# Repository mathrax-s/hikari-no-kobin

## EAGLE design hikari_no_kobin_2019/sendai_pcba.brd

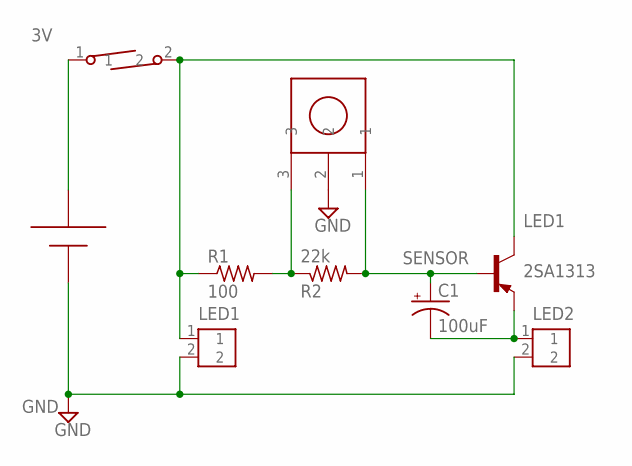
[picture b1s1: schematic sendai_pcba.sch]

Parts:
C1: 100uF; TT2D6
R1: 100; R0603
R2: 22k; R0603
T1: 2SA1313; SOT23-BEC
U$1: CR2032_VCR2032_V; CR2032_V
U$2, U$3: CONNECTER_CON2
U$4: LEAD_SWITCH_LEAD_SWITCH
U$5: OSRB38C9AA

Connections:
3V: U$1.3 (+), U$4.1
GND: U$1.2 (-), U$2.2, U$3.2, U$5.2
LED1: R1.1, T1.C, U$2.1, U$4.2
LED2: C1.-, T1.E, U$3.1
SENSOR: C1.+, R2.2, T1.B, U$5.1
V: R1.2, R2.1, U$5.3

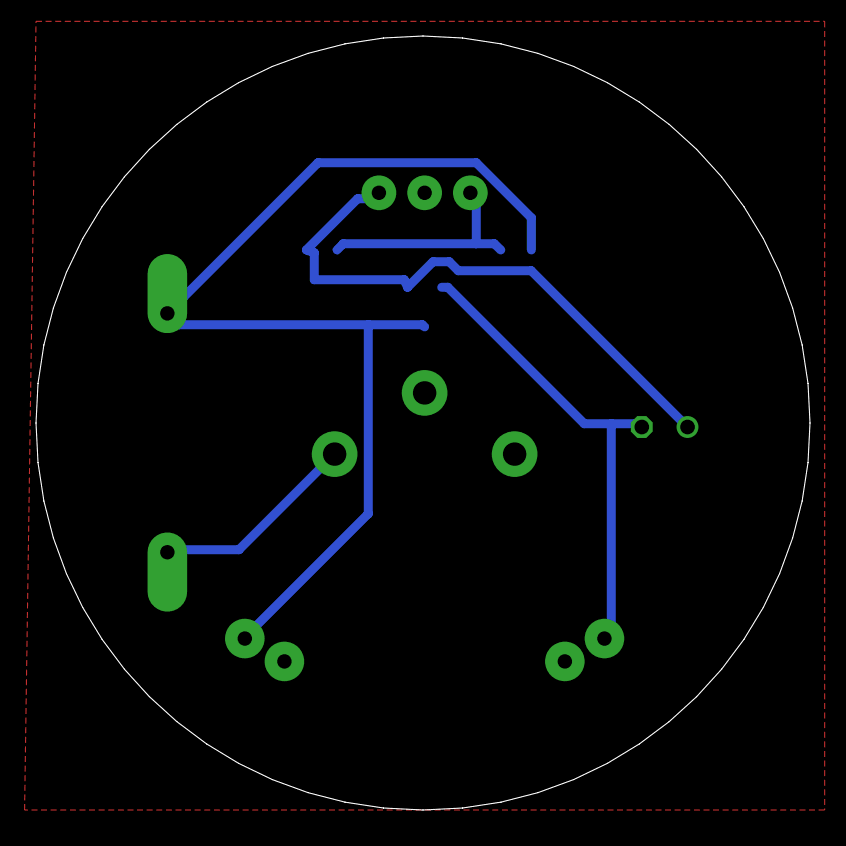
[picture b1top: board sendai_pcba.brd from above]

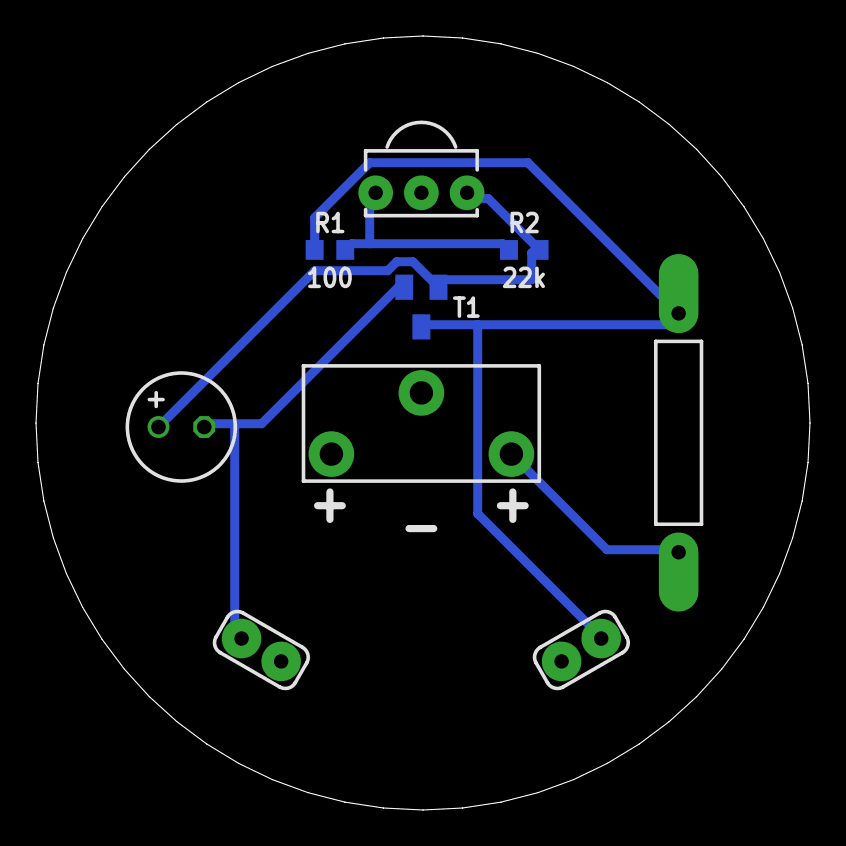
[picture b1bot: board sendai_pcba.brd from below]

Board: 2 copper layers, 43.0 x 43.0 mm, 9 parts (9 on the bottom side), 6 nets.

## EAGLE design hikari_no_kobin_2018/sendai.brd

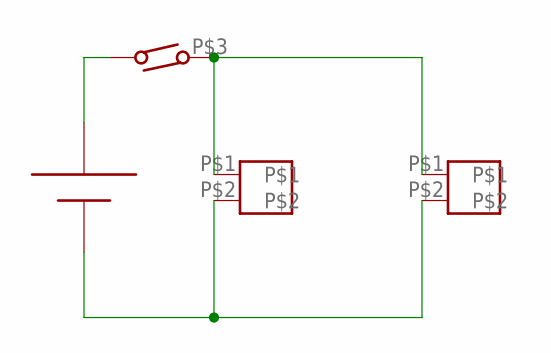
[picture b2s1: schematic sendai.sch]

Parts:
U$1: CR2032_CR2032
U$2, U$3: CONNECTER_CON2
U$4: LEAD_SWITCH_LEAD_SWITCH

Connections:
unnamed: U$2.P$1, U$3.P$1, U$4.P$3
unnamed: U$1.-1 (-), U$2.P$2, U$3.P$2
unnamed: U$1.P$1 (+), U$1.P$2 (+), U$4.P$4

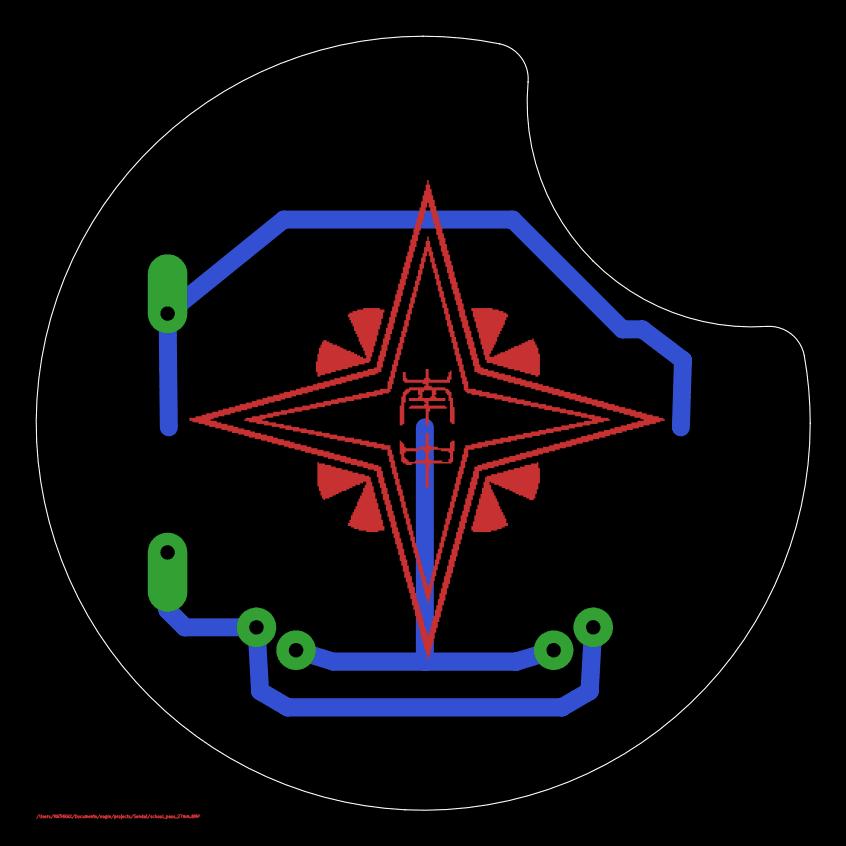
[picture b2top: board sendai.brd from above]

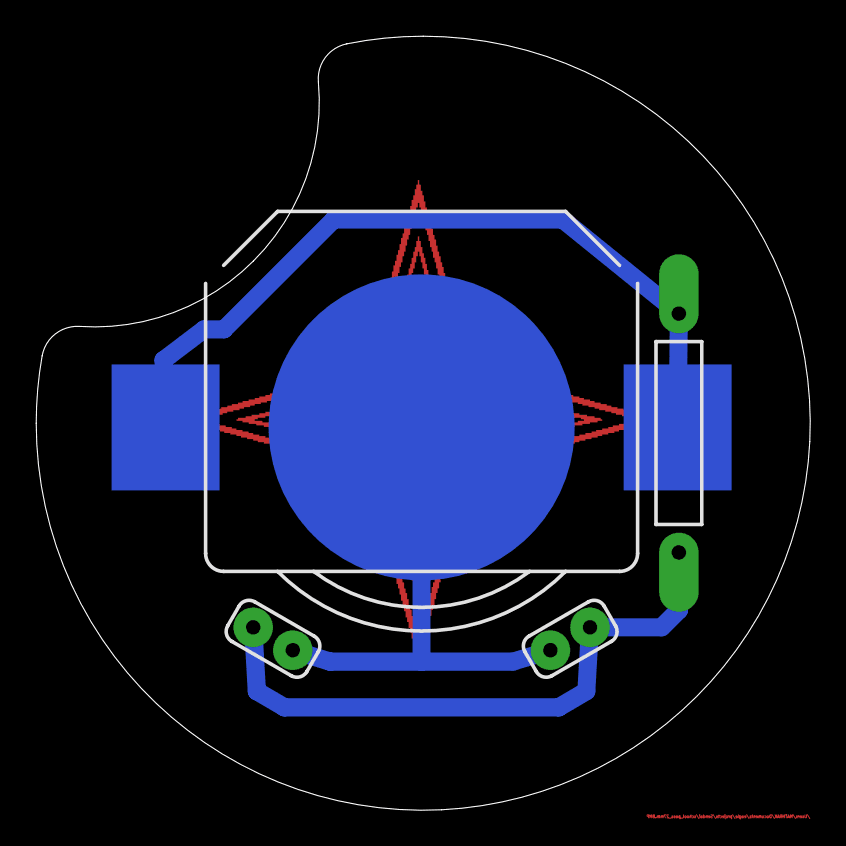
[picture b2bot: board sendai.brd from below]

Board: 2 copper layers, 43.0 x 43.0 mm, 4 parts (4 on the bottom side), 3 nets.

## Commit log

2019-05-11 基板データ
2019-09-05 20190905
2020-08-25 2020
    200pcs > 160pcs
